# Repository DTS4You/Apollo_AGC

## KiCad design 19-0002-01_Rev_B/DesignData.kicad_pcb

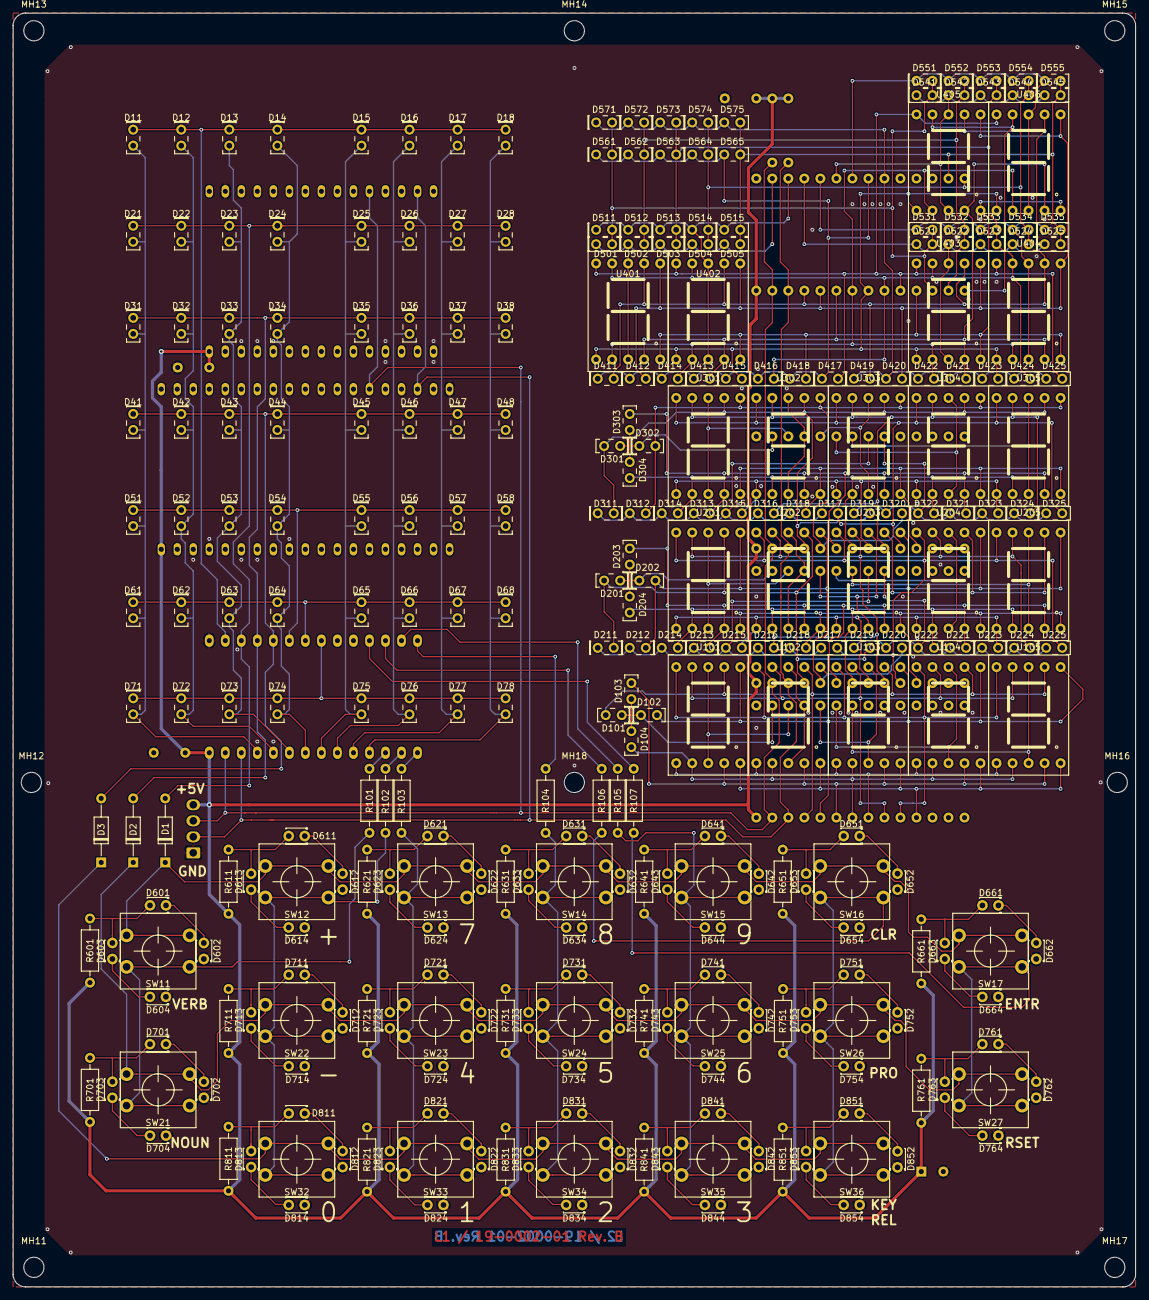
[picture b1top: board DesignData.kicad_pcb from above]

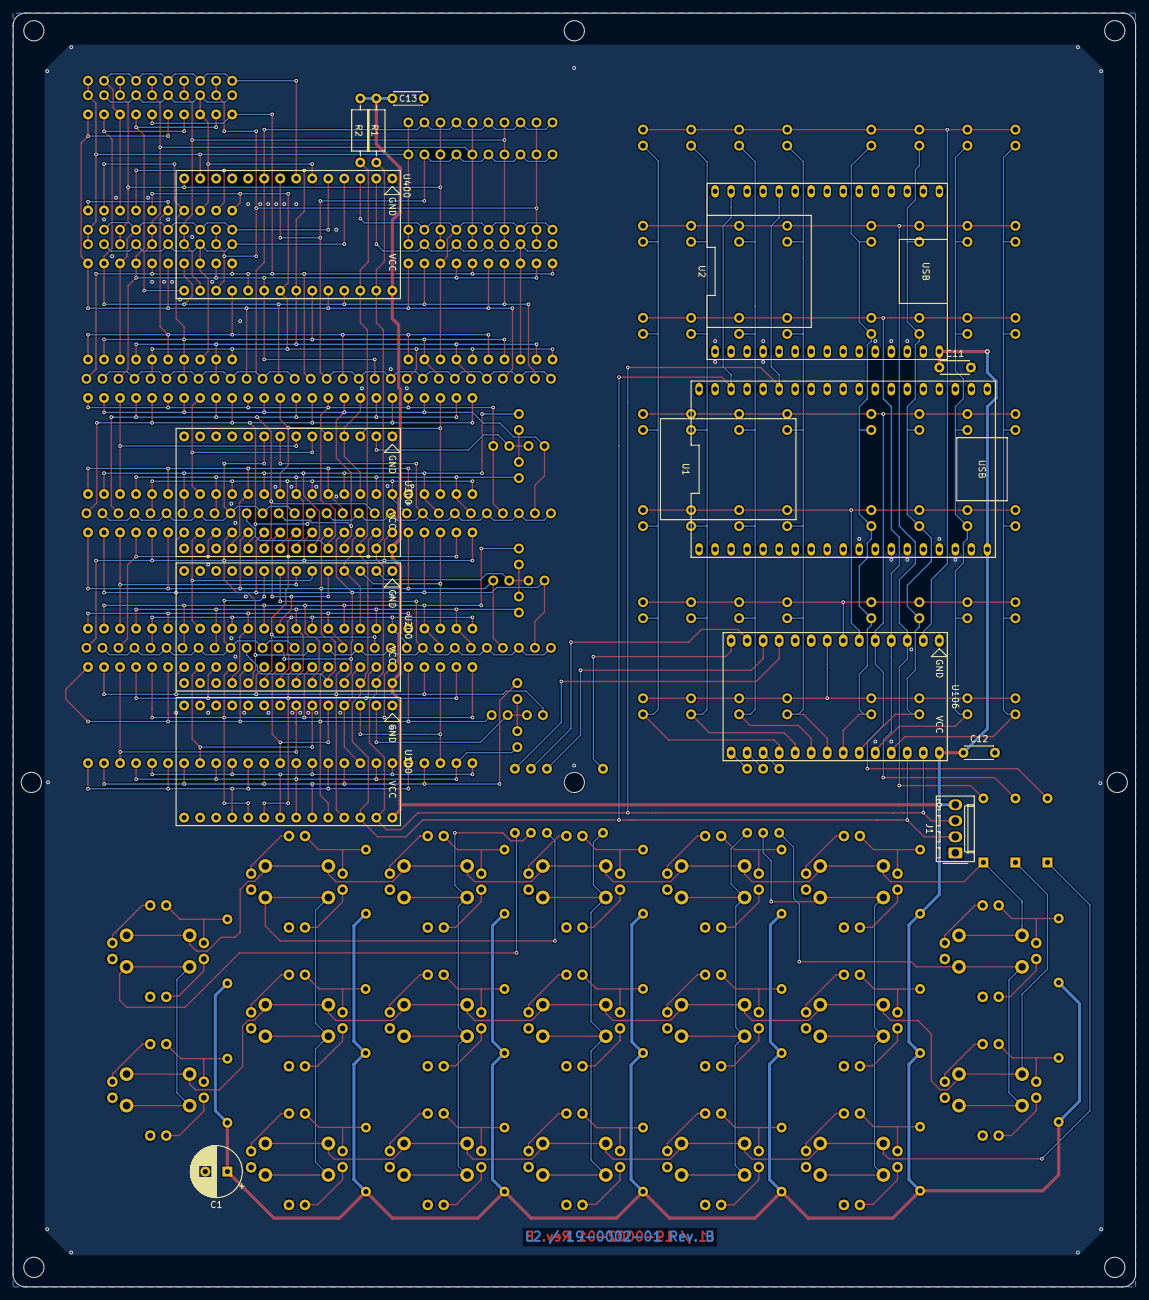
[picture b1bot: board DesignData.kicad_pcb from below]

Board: 2 copper layers, 178.0 x 202.0 mm, 320 parts (14 on the bottom side), 160 nets.

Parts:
C1: 47uF; CP_Radial_D8.0mm_P3.50mm
C11, C12, C13: 100n; C_Disc_D4.3mm_W1.9mm_P5.00mm
D1, D2, D3: 1N4148; D_DO-35_SOD27_P10.16mm_Horizontal
D11, D12, D13, D14, D15, D16, D17, D18, D21, D22, D23, D24, D25, D26, D27, D28, D31, D32, D33, D34, D35, D36, D37, D38, D41, D42, D43, D44, D45, D46, D47, D48, D51, D52, D53, D54, D55, D56, D57, D58, D61, D62, D63, D64, D65, D66, D67, D68, D71, D72, D73, D74, D75, D76, D77, D78, D101, D102, D103, D104, D201, D202, D203, D204, D211, D212, D213, D214, D215, D216, D217, D218, D219, D220, D221, D222, D223, D224, D225, D301, D302, D303, D304, D311, D312, D313, D314, D315, D316, D317, D318, D319, D320, D321, D322, D323, D324, D325, D411, D412, D413, D414, D415, D416, D417, D418, D419, D420, D421, D422, D423, D424, D425, D501, D502, D503, D504, D505, D511, D512, D513, D514, D515, D521, D522, D523, D524, D525, D531, D532, D533, D534, D535, D541, D542, D543, D544, D545, D551, D552, D553, D554, D555, D561, D562, D563, D564, D565, D571, D572, D573, D574, D575: LED; LED_Rectangular_W5.0mm_H2.0mm
D601, D602, D603, D604, D611, D612, D613, D614, D621, D622, D623, D624, D631, D632, D633, D634, D641, D642, D643, D644, D651, D652, D653, D654, D661, D662, D663, D664, D701, D702, D703, D704, D711, D712, D713, D714, D721, D722, D723, D724, D731, D732, D733, D734, D741, D742, D743, D744, D751, D752, D753, D754, D761, D762, D763, D764, D811, D812, D813, D814, D821, D822, D823, D824, D831, D832, D833, D834, D841, D842, D843, D844, D851, D852, D853, D854: LED; LED_D1.8mm_W3.3mm_H2.4mm_user
J1: Conn_01x04_Male; Molex_KK-254_AE-6410-04A_1x04_P2.54mm_Vertical
MH11, MH12, MH13, MH14, MH15, MH16, MH17, MH18: MountingHole_Pad; MountingHole_3.2mm_M3
R1, R2: 3K3; R_Axial_DIN0207_L6.3mm_D2.5mm_P10.16mm_Horizontal
R101, R102, R103, R104, R105, R106, R107: 39K; R_Axial_DIN0207_L6.3mm_D2.5mm_P10.16mm_Horizontal
R601, R611, R621, R631, R641, R651, R661, R701, R711, R721, R731, R741, R751, R761, R811, R821, R831, R841, R851: 120R; R_Axial_DIN0207_L6.3mm_D2.5mm_P10.16mm_Horizontal
SW11, SW12, SW13, SW14, SW15, SW16, SW17, SW21, SW22, SW23, SW24, SW25, SW26, SW27, SW32, SW33, SW34, SW35, SW36: SW_Push_45deg; SWITCH_THT_RACON_12
U1: ESP32-Modul_AZ; DIP-38_1000_ESP32
U2: ESP32-Modul_NodeMCU; DIP-30_1000_ESP32
U100, U106, U200, U300, U400: HT16K33_Modul
U101, U102, U103, U104, U105, U201, U202, U203, U204, U205, U301, U302, U303, U304, U305, U401, U402, U403, U404, U405, U406: SC56-11

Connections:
/Display_HT16K33_1/COM_0: D101.1, D102.1, D103.1, D104.1, U100.2
/Display_HT16K33_1/COM_1: U100.3, U101.3, U101.8
/Display_HT16K33_1/COM_2: U100.4, U102.3, U102.8
/Display_HT16K33_1/COM_3: U100.5, U103.3, U103.8
/Display_HT16K33_1/COM_4: U100.6, U104.3, U104.8
/Display_HT16K33_1/COM_5: U100.7, U105.3, U105.8
/Display_HT16K33_1/Seg_A: D101.2, U100.25, U101.7, U102.7, U103.7, U104.7, U105.7
/Display_HT16K33_1/Seg_B: D102.2, U100.24, U101.6, U102.6, U103.6, U104.6, U105.6
/Display_HT16K33_1/Seg_C: D103.2, U100.23, U101.4, U102.4, U103.4, U104.4, U105.4
/Display_HT16K33_1/Seg_D: D104.2, U100.22, U101.2, U102.2, U103.2, U104.2, U105.2
/Display_HT16K33_1/Seg_DP: U100.18, U101.5, U102.5, U103.5, U104.5, U105.5
/Display_HT16K33_1/Seg_E: U100.21, U101.1, U102.1, U103.1, U104.1, U105.1
/Display_HT16K33_1/Seg_F: U100.20, U101.9, U102.9, U103.9, U104.9, U105.9
/Display_HT16K33_1/Seg_G: U100.19, U101.10, U102.10, U103.10, U104.10, U105.10
/Display_HT16K33_2/COM_0: D201.1, D202.1, D203.1, D204.1, U200.2
/Display_HT16K33_2/COM_1: U200.3, U201.3, U201.8
/Display_HT16K33_2/COM_2: U200.4, U202.3, U202.8
/Display_HT16K33_2/COM_3: U200.5, U203.3, U203.8
/Display_HT16K33_2/COM_4: U200.6, U204.3, U204.8
/Display_HT16K33_2/COM_5: U200.7, U205.3, U205.8
/Display_HT16K33_2/COM_6: D211.1, D212.1, D213.1, D214.1, D215.1, D216.1, D217.1, D218.1, U200.8
/Display_HT16K33_2/COM_7: D219.1, D220.1, D221.1, D222.1, D223.1, D224.1, D225.1, U200.9
/Display_HT16K33_2/Seg_A: D201.2, D211.2, D219.2, U200.25, U201.7, U202.7, U203.7, U204.7, U205.7
/Display_HT16K33_2/Seg_B: D202.2, D212.2, D220.2, U200.24, U201.6, U202.6, U203.6, U204.6, U205.6
/Display_HT16K33_2/Seg_C: D203.2, D213.2, D221.2, U200.23, U201.4, U202.4, U203.4, U204.4, U205.4
/Display_HT16K33_2/Seg_D: D204.2, D214.2, D222.2, U200.22, U201.2, U202.2, U203.2, U204.2, U205.2
/Display_HT16K33_2/Seg_DP: D218.2, U200.18, U201.5, U202.5, U203.5, U204.5, U205.5
/Display_HT16K33_2/Seg_E: D215.2, D223.2, U200.21, U201.1, U202.1, U203.1, U204.1, U205.1
/Display_HT16K33_2/Seg_F: D216.2, D224.2, U200.20, U201.9, U202.9, U203.9, U204.9, U205.9
/Display_HT16K33_2/Seg_G: D217.2, D225.2, U200.19, U201.10, U202.10, U203.10, U204.10, U205.10
/Display_HT16K33_3/COM_0: D301.1, D302.1, D303.1, D304.1, U300.2
/Display_HT16K33_3/COM_1: U300.3, U301.3, U301.8
/Display_HT16K33_3/COM_2: U300.4, U302.3, U302.8
/Display_HT16K33_3/COM_3: U300.5, U303.3, U303.8
/Display_HT16K33_3/COM_4: U300.6, U304.3, U304.8
/Display_HT16K33_3/COM_5: U300.7, U305.3, U305.8
/Display_HT16K33_3/COM_6: D311.1, D312.1, D313.1, D314.1, D315.1, D316.1, D317.1, D318.1, U300.8
/Display_HT16K33_3/COM_7: D319.1, D320.1, D321.1, D322.1, D323.1, D324.1, D325.1, U300.9
/Display_HT16K33_3/Seg_A: D301.2, D311.2, D319.2, U300.25, U301.7, U302.7, U303.7, U304.7, U305.7
/Display_HT16K33_3/Seg_B: D302.2, D312.2, D320.2, U300.24, U301.6, U302.6, U303.6, U304.6, U305.6
/Display_HT16K33_3/Seg_C: D303.2, D313.2, D321.2, U300.23, U301.4, U302.4, U303.4, U304.4, U305.4
/Display_HT16K33_3/Seg_D: D304.2, D314.2, D322.2, U300.22, U301.2, U302.2, U303.2, U304.2, U305.2
/Display_HT16K33_3/Seg_DP: D318.2, U300.18, U301.5, U302.5, U303.5, U304.5, U305.5
/Display_HT16K33_3/Seg_E: D315.2, D323.2, U300.21, U301.1, U302.1, U303.1, U304.1, U305.1
/Display_HT16K33_3/Seg_F: D316.2, D324.2, U300.20, U301.9, U302.9, U303.9, U304.9, U305.9
/Display_HT16K33_3/Seg_G: D317.2, D325.2, U300.19, U301.10, U302.10, U303.10, U304.10, U305.10
/Display_HT16K33_4/COM_0: D501.1, D502.1, D503.1, D504.1, D505.1, U400.2, U401.3, U401.8
/Display_HT16K33_4/COM_1: D511.1, D512.1, D513.1, D514.1, D515.1, U400.3, U402.3, U402.8
/Display_HT16K33_4/COM_2: D521.1, D522.1, D523.1, D524.1, D525.1, U400.4, U403.3, U403.8
/Display_HT16K33_4/COM_3: D531.1, D532.1, D533.1, D534.1, D535.1, U400.5, U404.3, U404.8
/Display_HT16K33_4/COM_4: D541.1, D542.1, D543.1, D544.1, D545.1, U400.6, U405.3, U405.8
/Display_HT16K33_4/COM_5: D551.1, D552.1, D553.1, D554.1, D555.1, U400.7, U406.3, U406.8
/Display_HT16K33_4/COM_6: D411.1, D412.1, D413.1, D414.1, D415.1, D416.1, D417.1, D418.1, D561.1, D562.1, D563.1, D564.1, D565.1, U400.8
/Display_HT16K33_4/COM_7: D419.1, D420.1, D421.1, D422.1, D423.1, D424.1, D425.1, D571.1, D572.1, D573.1, D574.1, D575.1, U400.9
/Display_HT16K33_4/LED_1: D501.2, D511.2, D521.2, D531.2, D541.2, D551.2, D561.2, D571.2, U400.17
/Display_HT16K33_4/LED_2: D502.2, D512.2, D522.2, D532.2, D542.2, D552.2, D562.2, D572.2, U400.16
/Display_HT16K33_4/LED_3: D503.2, D513.2, D523.2, D533.2, D543.2, D553.2, D563.2, D573.2, U400.15
/Display_HT16K33_4/LED_4: D504.2, D514.2, D524.2, D534.2, D544.2, D554.2, D564.2, D574.2, U400.14
/Display_HT16K33_4/LED_5: D505.2, D515.2, D525.2, D535.2, D545.2, D555.2, D565.2, D575.2, U400.13
/Display_HT16K33_4/Seg_A: D411.2, D419.2, U400.25, U401.7, U402.7, U403.7, U404.7, U405.7, U406.7
/Display_HT16K33_4/Seg_B: D412.2, D420.2, U400.24, U401.6, U402.6, U403.6, U404.6, U405.6, U406.6
/Display_HT16K33_4/Seg_C: D413.2, D421.2, U400.23, U401.4, U402.4, U403.4, U404.4, U405.4, U406.4
/Display_HT16K33_4/Seg_D: D414.2, D422.2, U400.22, U401.2, U402.2, U403.2, U404.2, U405.2, U406.2
/Display_HT16K33_4/Seg_DP: D418.2, U400.18, U401.5, U402.5, U403.5, U404.5, U405.5, U406.5
/Display_HT16K33_4/Seg_E: D415.2, D423.2, U400.21, U401.1, U402.1, U403.1, U404.1, U405.1, U406.1
/Display_HT16K33_4/Seg_F: D416.2, D424.2, U400.20, U401.9, U402.9, U403.9, U404.9, U405.9, U406.9
/Display_HT16K33_4/Seg_G: D417.2, D425.2, U400.19, U401.10, U402.10, U403.10, U404.10, U405.10, U406.10
/LED_Key_HT16K33/COM_0: D11.1, D12.1, D13.1, D14.1, D15.1, D16.1, D17.1, D18.1, U106.2
/LED_Key_HT16K33/COM_1: D1.2, D21.1, D22.1, D23.1, D24.1, D25.1, D26.1, D27.1, D28.1, U106.3
/LED_Key_HT16K33/COM_2: D2.2, D31.1, D32.1, D33.1, D34.1, D35.1, D36.1, D37.1, D38.1, U106.4
/LED_Key_HT16K33/COM_3: D3.2, D41.1, D42.1, D43.1, D44.1, D45.1, D46.1, D47.1, D48.1, U106.5
/LED_Key_HT16K33/COM_4: D51.1, D52.1, D53.1, D54.1, D55.1, D56.1, D57.1, D58.1, U106.6
/LED_Key_HT16K33/COM_5: D61.1, D62.1, D63.1, D64.1, D65.1, D66.1, D67.1, D68.1, U106.7
/LED_Key_HT16K33/COM_6: D71.1, D72.1, D73.1, D74.1, D75.1, D76.1, D77.1, D78.1, U106.8
/LED_Key_HT16K33/K6: R101.1, U106.17
/LED_Key_HT16K33/K7: R102.1, U106.16
/LED_Key_HT16K33/K8: R103.1, U106.15
/LED_Key_HT16K33/K9: R104.1, U106.14
/LED_Key_HT16K33/K10: R105.1, U106.13
/LED_Key_HT16K33/K11: R106.1, U106.12
/LED_Key_HT16K33/K12: R107.1, U106.11
/LED_Key_HT16K33/KS_1: D1.1, SW11.2, SW12.2, SW13.2, SW14.2, SW15.2, SW16.2, SW17.2
/LED_Key_HT16K33/KS_2: D2.1, SW21.2, SW22.2, SW23.2, SW24.2, SW25.2, SW26.2, SW27.2
/LED_Key_HT16K33/KS_3: D3.1, SW32.2, SW33.2, SW34.2, SW35.2, SW36.2
/LED_Key_HT16K33/LED_0: D11.2, D21.2, D31.2, D41.2, D51.2, D61.2, D71.2, U106.25
/LED_Key_HT16K33/LED_1: D12.2, D22.2, D32.2, D42.2, D52.2, D62.2, D72.2, U106.24
/LED_Key_HT16K33/LED_2: D13.2, D23.2, D33.2, D43.2, D53.2, D63.2, D73.2, U106.23
/LED_Key_HT16K33/LED_3: D14.2, D24.2, D34.2, D44.2, D54.2, D64.2, D74.2, U106.22
/LED_Key_HT16K33/LED_4: D15.2, D25.2, D35.2, D45.2, D55.2, D65.2, D75.2, U106.21
/LED_Key_HT16K33/LED_5: D16.2, D26.2, D36.2, D46.2, D56.2, D66.2, D76.2, U106.20
/LED_Key_HT16K33/LED_6: D17.2, D27.2, D37.2, D47.2, D57.2, D67.2, D77.2, U106.19
/LED_Key_HT16K33/LED_7: D18.2, D28.2, D38.2, D48.2, D58.2, D68.2, D78.2, U106.18
GND: C1.2, C11.2, C12.2, C13.2, D602.1, D604.1, D612.1, D614.1, D622.1, D624.1, D632.1, D634.1, D642.1, D644.1, D652.1, D654.1, D662.1, D664.1, D702.1, D704.1, D712.1, D714.1, D722.1, D724.1, D732.1, D734.1, D742.1, D744.1, D752.1, D754.1, D762.1, D764.1, D812.1, D814.1, D822.1, D824.1, D832.1, D834.1, D842.1, D844.1, D852.1, D854.1, J1.1, U1.38, U2.17, U100.1, U106.1, U200.1, U300.1, U400.1
unnamed: D601.1, D602.2
unnamed: D601.2, D603.2, R601.2
unnamed: D603.1, D604.2
unnamed: D611.1, D612.2
unnamed: D611.2, D613.2, R611.2
unnamed: D613.1, D614.2
unnamed: D621.1, D622.2
unnamed: D621.2, D623.2, R621.2
unnamed: D623.1, D624.2
unnamed: D631.1, D632.2
unnamed: D631.2, D633.2, R631.2
unnamed: D633.1, D634.2
unnamed: D641.1, D642.2
unnamed: D641.2, D643.2, R641.2
unnamed: D643.1, D644.2
unnamed: D651.1, D652.2
unnamed: D651.2, D653.2, R651.2
unnamed: D653.1, D654.2
unnamed: D661.1, D662.2
unnamed: D661.2, D663.2, R661.2
unnamed: D663.1, D664.2
unnamed: D701.1, D702.2
unnamed: D701.2, D703.2, R701.2
unnamed: D703.1, D704.2
unnamed: D711.1, D712.2
unnamed: D711.2, D713.2, R711.2
unnamed: D713.1, D714.2
unnamed: D721.1, D722.2
unnamed: D721.2, D723.2, R721.2
unnamed: D723.1, D724.2
unnamed: D731.1, D732.2
unnamed: D731.2, D733.2, R731.2
unnamed: D733.1, D734.2
unnamed: D741.1, D742.2
unnamed: D741.2, D743.2, R741.2
unnamed: D743.1, D744.2
unnamed: D751.1, D752.2
unnamed: D751.2, D753.2, R751.2
unnamed: D753.1, D754.2
unnamed: D761.1, D762.2
unnamed: D761.2, D763.2, R761.2
unnamed: D763.1, D764.2
unnamed: D811.1, D812.2
unnamed: D811.2, D813.2, R811.2
unnamed: D813.1, D814.2
unnamed: D821.1, D822.2
unnamed: D821.2, D823.2, R821.2
unnamed: D823.1, D824.2
unnamed: D831.1, D832.2
unnamed: D831.2, D833.2, R831.2
unnamed: D833.1, D834.2
unnamed: D841.1, D842.2
unnamed: D841.2, D843.2, R841.2
unnamed: D843.1, D844.2
unnamed: D851.1, D852.2
unnamed: D851.2, D853.2, R851.2
unnamed: D853.1, D854.2
unnamed: R101.2, SW11.1, SW21.1
unnamed: R102.2, SW12.1, SW22.1, SW32.1
unnamed: R103.2, SW13.1, SW23.1, SW33.1
unnamed: R104.2, SW14.1, SW24.1, SW34.1
unnamed: R105.2, SW15.1, SW25.1, SW35.1
unnamed: R106.2, SW16.1, SW26.1, SW36.1
unnamed: R107.2, SW17.1, SW27.1
SCL: J1.2, R2.2, U1.36, U2.29, U100.26, U106.26, U200.26, U300.26, U400.26
SDA: J1.3, R1.2, U1.33, U2.26, U100.27, U106.27, U200.27, U300.27, U400.27
VCC: C1.1, C11.1, C12.1, C13.1, J1.4, R1.1, R2.1, R601.1, R611.1, R621.1, R631.1, R641.1, R651.1, R661.1, R701.1, R711.1, R721.1, R731.1, R741.1, R751.1, R761.1, R811.1, R821.1, R831.1, R841.1, R851.1, U1.19, U2.15, U100.28, U106.28, U200.28, U300.28, U400.28

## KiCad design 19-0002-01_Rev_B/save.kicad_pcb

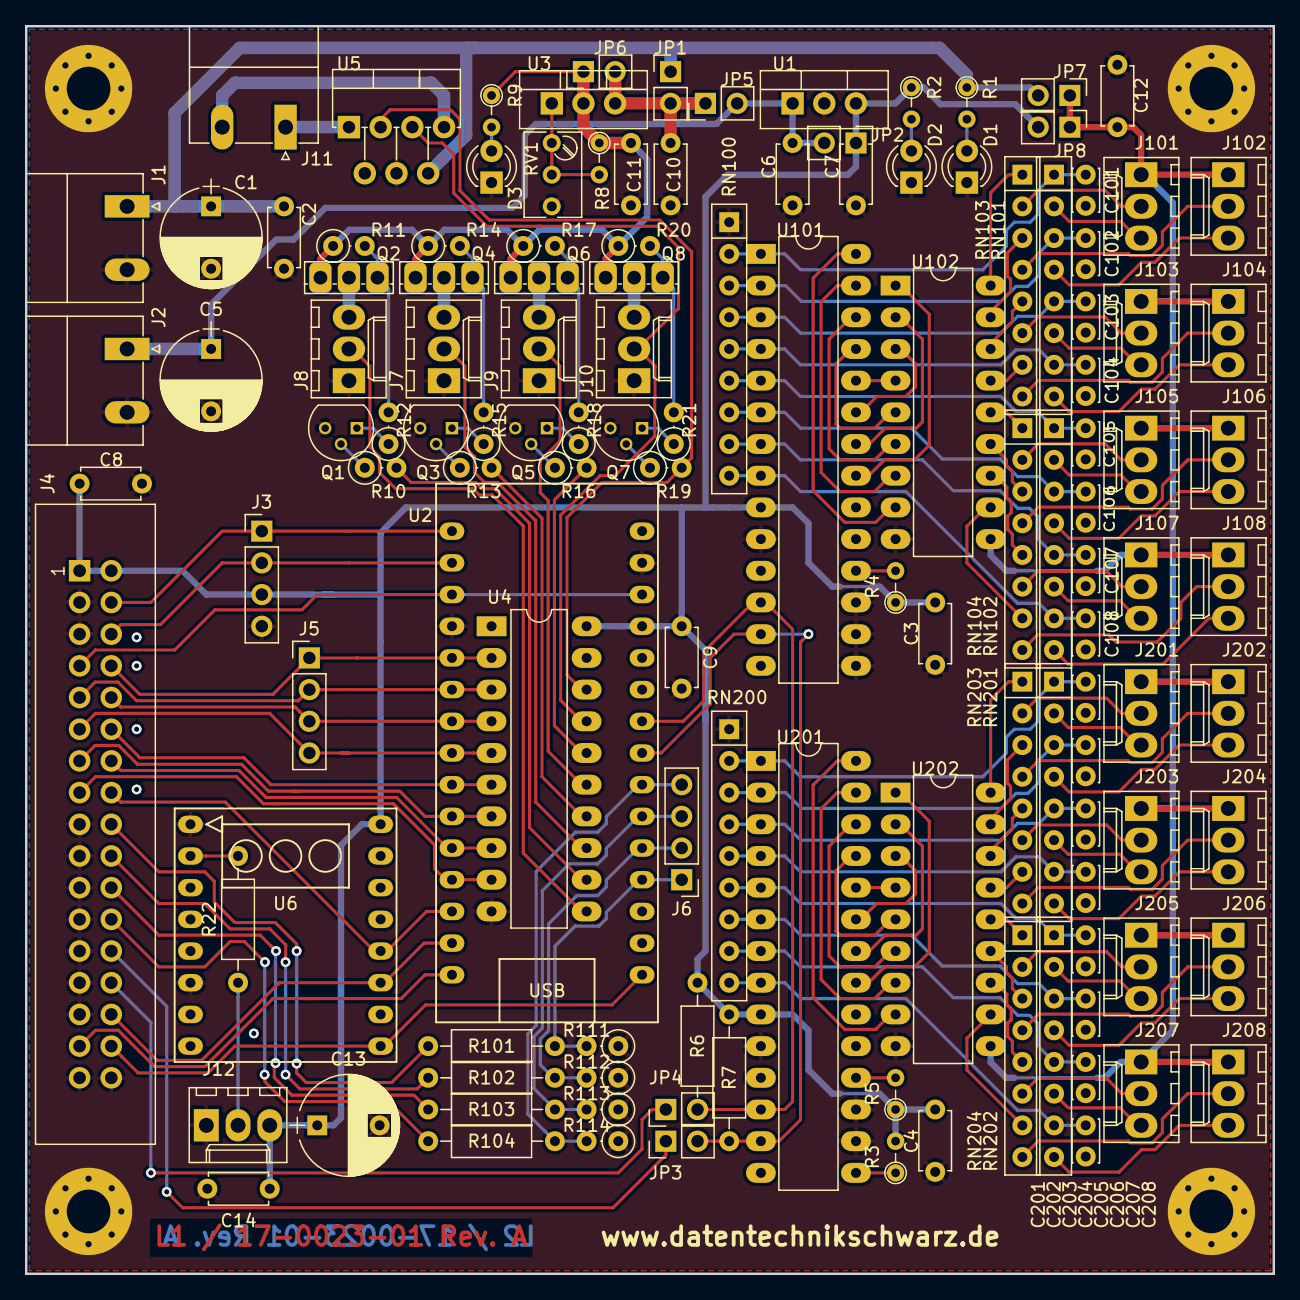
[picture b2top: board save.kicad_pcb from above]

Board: 2 copper layers, 100.0 x 100.0 mm, 132 parts (0 on the bottom side), 149 nets.

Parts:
C1, C5, C13: 47uF; CP_Radial_D8.0mm_P5.00mm
C2, C3, C4, C6, C7, C8, C9, C10, C11, C12, C14: 100nF; C_Disc_D4.7mm_W2.5mm_P5.00mm
C101, C102, C103, C104, C105, C106, C107, C108, C201, C202, C203, C204, C205, C206, C207, C208: 100nF; C_Disc_D3.4mm_W2.1mm_P2.50mm
D1, D2, D3: LED; LED_D3.0mm
J1, J2, J11: Screw_Terminal_1x02; PhoenixContact_MC-G_02x5.08mm_Angled
J3, J5, J6: CONN_01X04; Pin_Header_Straight_1x04_Pitch2.54mm
J4: CONN_02X17; IDC_Header_Straight_34pins
J7, J8, J9, J10, J12, J101, J102, J103, J104, J105, J106, J107, J108, J201, J202, J203, J204, J205, J206, J207, J208: CONN_01X03; Molex_KK-6410-03_03x2.54mm_Straight
J1001, J1002, J1003, J1004: TEST_1P; MountingHole_3.5mm_Pad_Via
JP1, JP2, JP5, JP6, JP7, JP8: Jumper_NO_Small; Pin_Header_Straight_1x02_Pitch2.54mm
JP3, JP4: Jumper_NC_Small; Pin_Header_Straight_1x02_Pitch2.54mm
Q1, Q3, Q5, Q7: BC547; TO-92_Molded_Narrow
Q2, Q4, Q6, Q8: IRF9024N; TO-251_IPAK_Vertical_user
R1, R2, R9: 390R; R_Axial_DIN0204_L3.6mm_D1.6mm_P2.54mm_Vertical
R3, R4, R5: 10K; R_Axial_DIN0204_L3.6mm_D1.6mm_P2.54mm_Vertical
R6, R7: 3K3; R_Axial_DIN0207_L6.3mm_D2.5mm_P10.16mm_Horizontal
R8: 270R; R_Axial_DIN0204_L3.6mm_D1.6mm_P2.54mm_Vertical
R10, R12, R13, R15, R16, R18, R19, R21: 4K7; R_Axial_DIN0207_L6.3mm_D2.5mm_P2.54mm_Vertical
R11, R14, R17, R20: 47K; R_Axial_DIN0207_L6.3mm_D2.5mm_P2.54mm_Vertical
R22: 330R; R_Axial_DIN0207_L6.3mm_D2.5mm_P10.16mm_Horizontal
R101, R102, R103, R104: 100R; R_Axial_DIN0207_L6.3mm_D2.5mm_P10.16mm_Horizontal
R111, R112, R113, R114: 10K; R_Axial_DIN0207_L6.3mm_D2.5mm_P2.54mm_Vertical
RN100, RN200: 10K; R_Array_SIP9
RN101, RN102, RN201, RN202: 1K0; R_Array_SIP8
RN103, RN104, RN203, RN204: 180R; R_Array_SIP8
RV1: 5K0; Potentiometer_Trimmer_Bourns_3266Y
U1: LM7805_TO220; TO-220_Vertical
U2: Arduino_Nano
U3: LM317_3PinPackage; TO-220_Vertical
U4: 74HC245; DIP-20_W7.62mm_LongPads
U5: TLE5206-2; TO-220-7_Multiwatt-7_Vertical_StaggeredType2
U6: Digi_Dot_Booster
U101, U201: MCP23017; DIP-28_W7.62mm_LongPads
U102, U202: ULN2803A; DIP-18_W7.62mm_LongPads

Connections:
/SCL_ext: J4.28, JP4.1
/SDA_ext: J4.26, JP3.1
AN_0: J6.1, R101.1, R111.2, U2.19
AN_1: J6.2, R102.1, R112.2, U2.20
AN_2: J6.3, R103.1, R113.2, U2.21
AN_3: J6.4, R104.1, R114.2, U2.22
GND: C1.2, C2.2, C3.2, C4.2, C5.2, C6.2, C7.2, C8.2, C9.2, C10.2, C11.2, C12.2, C13.2, C14.2, C101.2, C102.2, C103.2, C104.2, C105.2, C106.2, C107.2, C108.2, C201.2, C202.2, C203.2, C204.2, C205.2, C206.2, C207.2, C208.2, D1.1, D2.1, D3.1, J1.2, J2.2, J3.4, J4.3, J4.5, J4.17, J4.19, J4.21, J4.23, J4.25, J4.27, J4.29, J4.33, J4.34, J7.1, J8.1, J9.1, J10.1, J12.1, J1001.1, J1002.1, J1003.1, J1004.1, Q1.3, Q3.3, Q5.3, Q7.3, R111.1, R112.1, R113.1, R114.1, RN100.1, RN200.1, RV1.3, U1.2, U2.4, U2.29, U4.10, U5.4, U6.1, U6.6, U101.10, U101.15, U101.16, U101.17, U102.9, U201.10, U201.16, U201.17, U202.9
I1.1: J101.3, RN101.2
I1.2: J102.3, RN101.4
I1.3: J103.3, RN101.6
I1.4: J104.3, RN101.8
I1.5: J105.3, RN102.2
I1.6: J106.3, RN102.4
I1.7: J107.3, RN102.6
I1.8: J108.3, RN102.8
I2.1: J201.3, RN201.2
I2.2: J202.3, RN201.4
I2.3: J203.3, RN201.6
I2.4: J204.3, RN201.8
I2.5: J205.3, RN202.2
I2.6: J206.3, RN202.4
I2.7: J207.3, RN202.6
I2.8: J208.3, RN202.8
IO_0: J4.8, J5.1, U2.5, U4.2
IO_1: J4.9, J5.2, U2.6, U4.3
IO_2: J4.10, J5.3, U2.7, U4.4
IO_3: J4.11, J5.4, U2.8, U4.5
IO_4: J4.12, U2.9, U4.6
IO_5: J4.13, U2.10, U4.7
IO_6: J4.14, U2.11, U4.8
IO_7: J4.15, U2.12, U4.9
IO_8: J4.16, U2.13, U6.12
MISO: J4.31, U2.15
MOSI: J4.30, U2.14, U6.11
unnamed: C10.1, JP1.2, JP5.1, JP6.2, U3.3
unnamed: C101.1, RN100.2, RN101.1, U101.1
unnamed: C102.1, RN100.3, RN101.3, U101.2
unnamed: C103.1, RN100.4, RN101.5, U101.3
unnamed: C104.1, RN100.5, RN101.7, U101.4
unnamed: C105.1, RN100.6, RN102.1, U101.5
unnamed: C106.1, RN100.7, RN102.3, U101.6
unnamed: C107.1, RN100.8, RN102.5, U101.7
unnamed: C108.1, RN100.9, RN102.7, U101.8
unnamed: C201.1, RN200.2, RN201.1, U201.1
unnamed: C202.1, RN200.3, RN201.3, U201.2
unnamed: C203.1, RN200.4, RN201.5, U201.3
unnamed: C204.1, RN200.5, RN201.7, U201.4
unnamed: C205.1, RN200.6, RN202.1, U201.5
unnamed: C206.1, RN200.7, RN202.3, U201.6
unnamed: C207.1, RN200.8, RN202.5, U201.7
unnamed: C208.1, RN200.9, RN202.7, U201.8
unnamed: D1.2, R1.2
unnamed: D2.2, R2.2
unnamed: D3.2, R9.2
unnamed: J4.18, R101.2
unnamed: J4.20, R102.2
unnamed: J4.22, R103.2
unnamed: J4.24, R104.2
unnamed: J7.3, Q4.2
unnamed: J8.3, Q2.2
unnamed: J9.3, Q6.2
unnamed: J10.3, Q8.2
unnamed: J11.1, U5.1
unnamed: J11.2, U5.7
unnamed: J12.2, R22.1
unnamed: Q1.1, R12.1
unnamed: Q1.2, R10.1
unnamed: Q2.1, R11.2, R12.2
unnamed: Q3.1, R15.1
unnamed: Q3.2, R13.1
unnamed: Q4.1, R14.2, R15.2
unnamed: Q5.1, R18.1
unnamed: Q5.2, R16.1
unnamed: Q6.1, R17.2, R18.2
unnamed: Q7.1, R21.1
unnamed: Q7.2, R19.1
unnamed: Q8.1, R20.2, R21.2
unnamed: R3.1, U201.15
unnamed: R4.2, U101.18
unnamed: R5.2, U201.18
unnamed: R8.2, RV1.1, RV1.2, U3.1
unnamed: RN103.1, U102.18
unnamed: RN103.3, U102.17
unnamed: RN103.5, U102.16
unnamed: RN103.7, U102.15
unnamed: RN104.1, U102.14
unnamed: RN104.3, U102.13
unnamed: RN104.5, U102.12
unnamed: RN104.7, U102.11
unnamed: RN203.1, U202.18
unnamed: RN203.3, U202.17
unnamed: RN203.5, U202.16
unnamed: RN203.7, U202.15
unnamed: RN204.1, U202.14
unnamed: RN204.3, U202.13
unnamed: RN204.5, U202.12
unnamed: RN204.7, U202.11
unnamed: U101.21, U102.1
unnamed: U101.22, U102.2
unnamed: U101.23, U102.3
unnamed: U101.24, U102.4
unnamed: U101.25, U102.5
unnamed: U101.26, U102.6
unnamed: U101.27, U102.7
unnamed: U101.28, U102.8
unnamed: U201.21, U202.1
unnamed: U201.22, U202.2
unnamed: U201.23, U202.3
unnamed: U201.24, U202.4
unnamed: U201.25, U202.5
unnamed: U201.26, U202.6
unnamed: U201.27, U202.7
unnamed: U201.28, U202.8
Q1.1: J101.2, RN103.2
Q1.2: J102.2, RN103.4
Q1.3: J103.2, RN103.6
Q1.4: J104.2, RN103.8
Q1.5: J105.2, RN104.2
Q1.6: J106.2, RN104.4
Q1.7: J107.2, RN104.6
Q1.8: J108.2, RN104.8
Q2.1: J201.2, RN203.2
Q2.2: J202.2, RN203.4
Q2.3: J203.2, RN203.6
Q2.4: J204.2, RN203.8
Q2.5: J205.2, RN204.2
Q2.6: J206.2, RN204.4
Q2.7: J207.2, RN204.6
Q2.8: J208.2, RN204.8
RX: J3.2, J4.6, U2.2
Reset: J4.7, U2.3, U2.28
SCK: J4.32, U2.16, U6.9
SCL: JP4.2, R6.2, U2.24, U101.12, U201.12
SDA: JP3.2, R7.2, U2.23, U101.13, U201.13
Servo_0_POW: R10.2, U4.12
Servo_0_PWM: J8.2, U4.11
Servo_1_POW: R13.2, U4.14
Servo_1_PWM: J7.2, U4.13
Servo_2_POW: R16.2, U4.16
Servo_2_PWM: J9.2, U4.15
Servo_3_POW: R19.2, U4.18, U5.3
Servo_3_PWM: J10.2, U4.17, U5.5
TX: J3.1, J4.4, U2.1
VBUS: C5.1, C6.1, J2.1, JP2.2, JP5.2, U1.1
VCC: C3.1, C4.1, C7.1, C8.1, C9.1, C13.1, C14.1, J3.3, J4.1, J4.2, J12.3, JP2.1, JP8.2, R2.1, R3.2, R4.1, R5.1, R6.1, R7.1, U1.3, U2.27, U4.20, U6.16, U101.9, U201.9
VDD: C1.1, C2.1, J1.1, JP1.1, JP7.2, R1.1, U5.6
VDDA: C11.1, JP6.1, Q2.3, Q4.3, Q6.3, Q8.3, R8.1, R9.1, R11.1, R14.1, R17.1, R20.1, U3.2
V_IO: C12.1, J101.1, J102.1, J103.1, J104.1, J105.1, J106.1, J107.1, J108.1, J201.1, J202.1, J203.1, J204.1, J205.1, J206.1, J207.1, J208.1, JP7.1, JP8.1, U102.10, U202.10
WS2812: R22.2, U6.2

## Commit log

2019-03-31 New file
2019-03-31 Revision angepasst
2019-03-31 in work
